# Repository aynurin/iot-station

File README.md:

# Nour Eggboard

This is a main board of a low-power battery powered IoT device controller based on ESP8266 (ESP-WROOM-02) that drives peripheral devices on I2C bus.

Currenly the project is under development and you can help in the following way:

* Suggest new features and report bugs
* Submit pull requests
* Help fund the development by [donating via PayPal](https://www.paypal.com/donate?business=M5DEYMX2BZ4MJ&no_recurring=0&item_name=Help+support+Nour+Eggboard+development&currency_code=USD)

## LICENSE

Currently this project is licensed as  [GNU AGPLv3](./LICENSE). This is intended to be changed to Apache or MIT when I get a better feel of the project and see how it moves forward. I would accept suggestions of a qualified lawyer as I need help figuring out how to move forward.

## How is this helpful

Most prototyping boards are exactly what they say - designed for prototyping and difficult to apply in a production device or if you are a hardcore hobbyist. Unlike those projects, the Eggboard is intended to be a final solution that lets you hook your peripherals to an I2C bus and enjoy a low-power battery operation, wireless charging, and WiFi connectivity out of the box.

Features:

* WiFi capability via ESP8266
* Own I2C port that allows I2C communication, sleep power line, ability to operate when host sleeps, and a host wakeup channel
* Customizable (via resistance change) sleep timer that drives the host and all of the peripherals
* Battery operation
* Wireless and USB-C charging
* USB-C programming via esptool or Arduino IDE (and other compatible IDEs and methods)

## Nour Egg Plant station

The example implementation is a Nour Egg plant ecosystem controller that is under development. This device is going to be commercially available for purchase in 2022 along with free downloadable app and a cloud-based analytics platform.

Key features of the Nour Egg:

* Monitor air quality, soil moisture, and lighting conditions of your home plant
* Low-power operation that runs for months on a single charge, and wireless charging
* WiFi connectivity to report statistics to the cloud and Nour Egg app
* Appealing look and feel in a nice shell and beautiful RGB light indicators

Implemented peripherals:

* Soil moisture sensor based on capacitance sensing using a coplanar capacitor probe
* Air quality sensor
* Light sensor
* LED indicators board driving 18 leds or 6 RGB leds

## Roadmap

The versioning works by bird names, e.g. see [WhatBird.com NA Birds by Size](https://www.whatbird.com/browse/attribute/birds_na_147/51/Size/):

| Milestone | Release Date | Focus |
|---|---|---|
| [Pine Siskin](https://github.com/aynurin/iot-station/milestone/1) | September 2021 | Hardware design |
| [Pygmy Nuthatch](https://github.com/aynurin/iot-station/milestone/2) | December 2021 | PoC Cloud and App |
| [Winter Wren](https://github.com/aynurin/iot-station/milestone/3) | March 2022 | Production feasible enclosure |
| [Hutton's Vireo](https://github.com/aynurin/iot-station/milestone/4) | June 2022 | Production feasible hardware, test board production |
.

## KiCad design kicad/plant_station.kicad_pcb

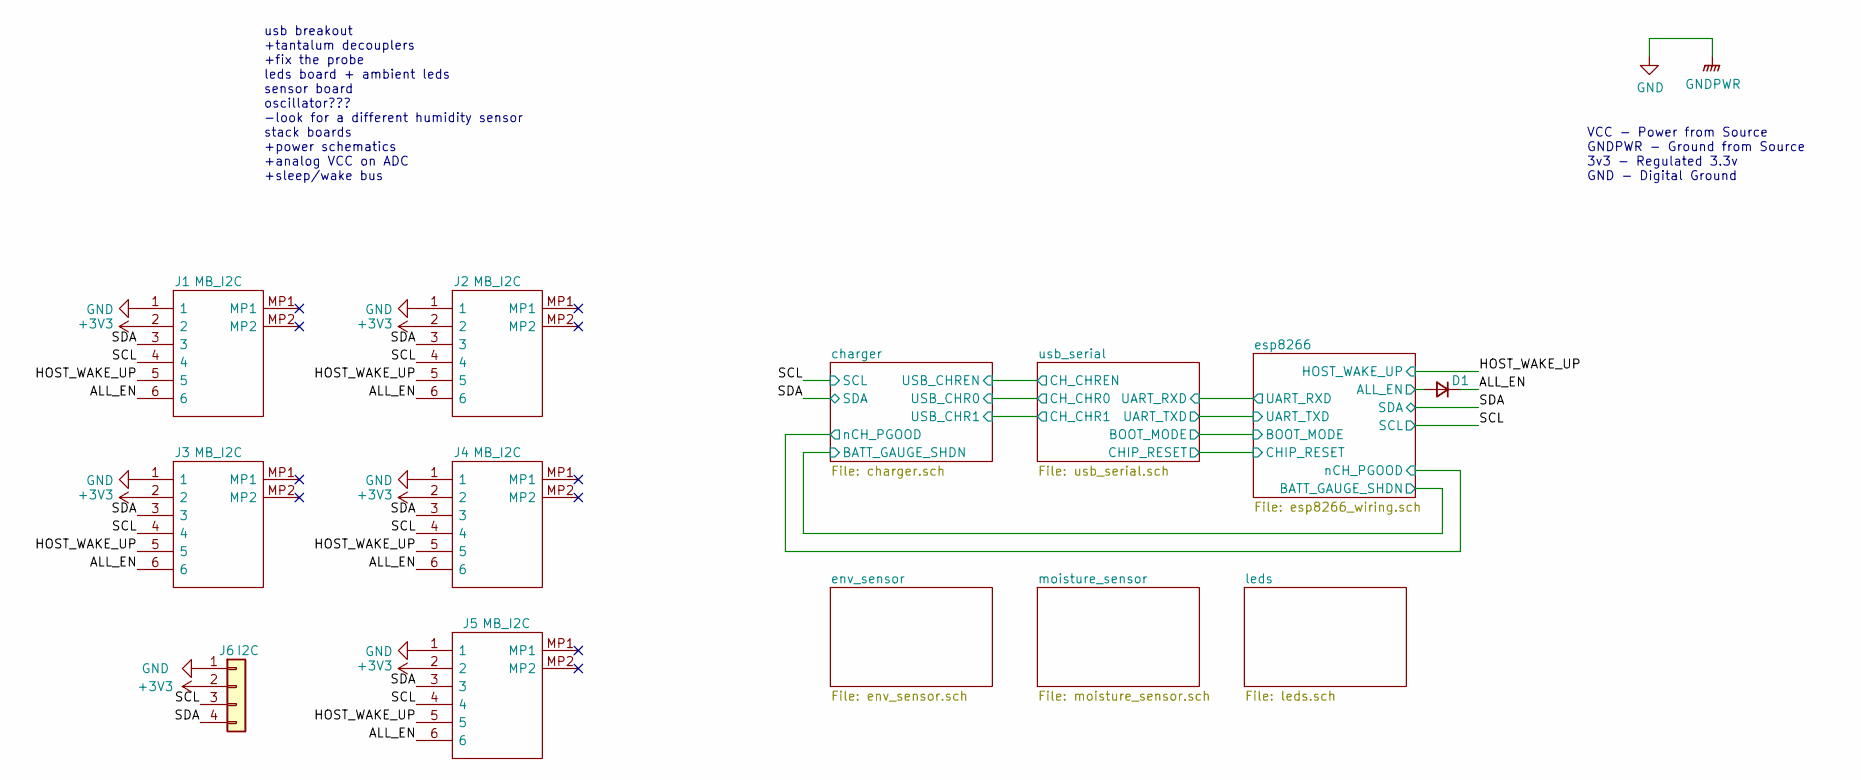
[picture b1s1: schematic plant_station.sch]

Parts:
D1: LS4148; MELF_SOD_80_3_BZT55B13GS08
J1, J2, J3, J4, J5: MB_I2C; Molex_Conn_SMD_01x06_505567_0671; Manufacturer_Part_Number 505567-0671; Mouser Part Number 538-505567-0671
J6: I2C; PinSocket_1x04_P2.54mm_Vertical

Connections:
/ALL_EN: D1.1 (K), J1.6, J2.6, J3.6, J4.6, J5.6
/HOST_WAKE_UP: J1.5, J2.5, J3.5, J4.5, J5.5; also elsewhere on the board
/SCL: J1.4, J2.4, J3.4, J4.4, J5.4, J6.3; also elsewhere on the board
/SDA: J1.3, J2.3, J3.3, J4.3, J5.3, J6.4; also elsewhere on the board
/esp8266/ALL_EN: D1.2 (A); also elsewhere on the board
GND: J1.1, J2.1, J3.1, J4.1, J5.1, J6.1; also elsewhere on the board

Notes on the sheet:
usb breakout +tantalum decouplers +fix the probe leds board + ambient leds sensor board oscillator??? -look for a different humidity sensor stack boards +power schematics +analog VCC on ADC +sleep/wake bus
VCC - Power from Source GNDPWR - Ground from Source 3v3 - Regulated 3.3v GND - Digital Ground

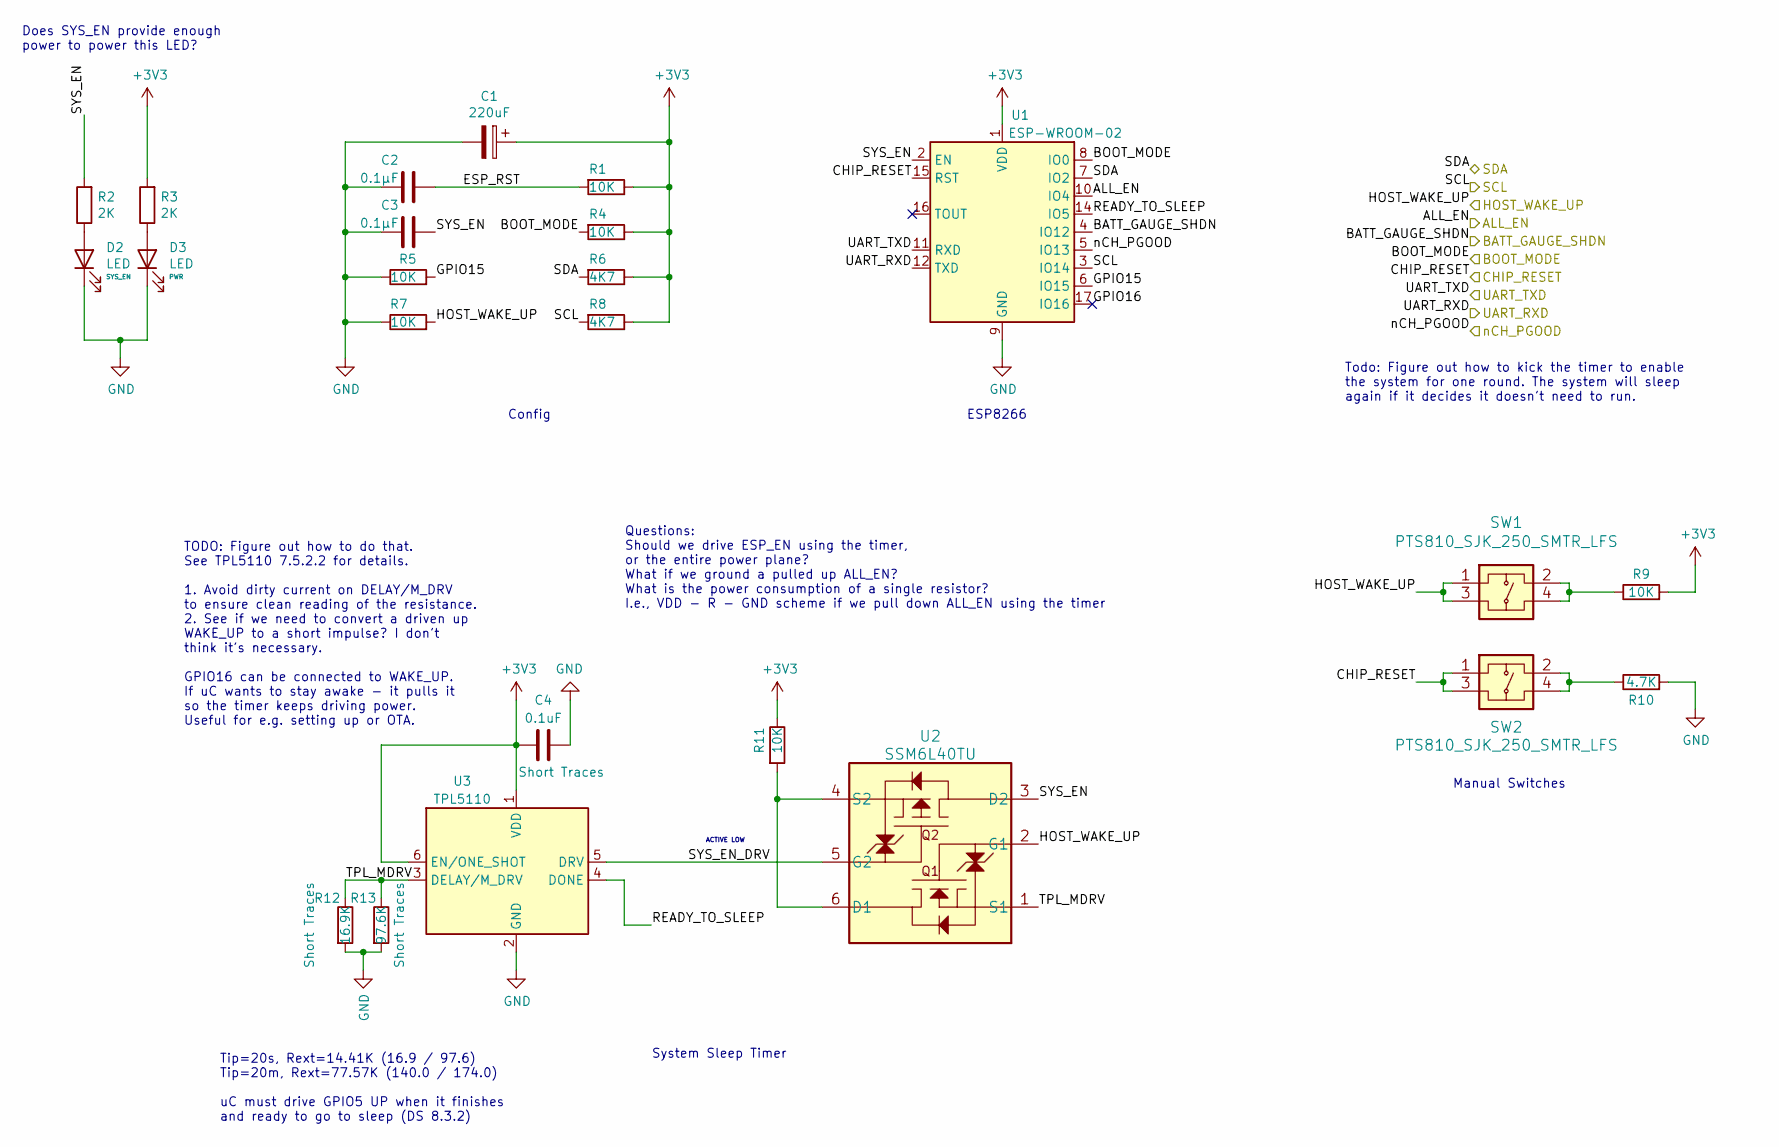
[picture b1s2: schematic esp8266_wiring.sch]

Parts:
C1: 220uF; CP_EIA-3216-18_Kemet-A
C2, C3: 0.1μF; C_1206_3216Metric
C4: 0.1uF; C_1206_3216Metric
D2, D3: LED; LED_0603_1608Metric
R1, R4, R5, R7, R9, R11: 10K; R_0805_2012Metric
R2, R3: 2K; R_0805_2012Metric
R6, R8: 4K7; R_0805_2012Metric
R10: 4.7K; R_0805_2012Metric
R12: 16.9K; R_0805_2012Metric
R13: 97.6K; R_0805_2012Metric
SW1, SW2: PTS810_SJK_250_SMTR_LFS; PTS810SJK250SMTRLFS
U1: ESP-WROOM-02
U2: SSM6L40TU
U3: TPL5110; SOT-23-6

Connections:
/HOST_WAKE_UP: R7.2, SW1.1, SW1.3, U2.2 (G1); also elsewhere on the board
/SCL: R8.2, U1.3 (IO14); also elsewhere on the board
/SDA: R6.2, U1.7 (IO2); also elsewhere on the board
/charger/BATT_GAUGE_SHDN: U1.4 (IO12); also elsewhere on the board
/charger/nCH_PGOOD: U1.5 (IO13); also elsewhere on the board
/esp8266/ALL_EN: U1.10 (IO4); also elsewhere on the board
/esp8266/BOOT_MODE: R4.2, U1.8 (IO0); also elsewhere on the board
/esp8266/CHIP_RESET: SW2.1, SW2.3, U1.15 (RST); also elsewhere on the board
/esp8266/ESP_RST: C2.2, R1.2
/esp8266/GPIO15: R5.2, U1.6 (IO15)
/esp8266/GPIO16: U1.17 (IO16)
/esp8266/READY_TO_SLEEP: U1.14 (IO5), U3.4 (DONE)
/esp8266/SYS_EN: C3.2, R2.2, U1.2 (EN), U2.3 (D2)
/esp8266/SYS_EN_DRV: U2.5 (G2), U3.5 (DRV)
/esp8266/TPL_MDRV: R12.1, R13.1, U2.1 (S1), U3.3 (DELAY/M_DRV)
/esp8266/UART_RXD: U1.12 (TXD); also elsewhere on the board
/esp8266/UART_TXD: U1.11 (RXD); also elsewhere on the board
GND: C1.2, C2.1, C3.1, C4.1, D2.1 (K), D3.1 (K), R5.1, R7.1, R10.2, R12.2, R13.2, U1.9 (GND), U1.13 (GND), U1.18 (GND), U1.19 (GND), U3.2 (GND); also elsewhere on the board
unnamed: D2.2 (A), R2.1
unnamed: D3.2 (A), R3.1
unnamed: R9.1, SW1.2, SW1.4
unnamed: R10.1, SW2.2, SW2.4
unnamed: R11.2, U2.4 (S2), U2.6 (D1)

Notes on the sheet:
Config
System Sleep Timer
Tip=20s, Rext=14.41K (16.9 / 97.6) Tip=20m, Rext=77.57K (140.0 / 174.0) uC must drive GPIO5 UP when it finishes and ready to go to sleep (DS 8.3.2)
TODO: Figure out how to do that. See TPL5110 7.5.2.2 for details. 1. Avoid dirty current on DELAY/M_DRV to ensure clean reading of the resistance. 2. See if we need to convert a driven up WAKE_UP to a short impulse? I don't think it's necessary. GPIO16 can be connected to WAKE_UP. If uC wants to st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
Questions: Should we drive ESP_EN using the timer, or the entire power plane? What if we ground a pulled up ALL_EN? What is the power consumption of a single resistor? I.e., VDD - R - GND scheme if we pull down ALL_EN using the timer
ACTIVE LOW
ESP8266
Does SYS_EN provide enough power to power this LED?
Manual Switches
Todo: Figure out how to kick the timer to enable the system for one round. The system will sleep again if it decides it doesn't need to run.

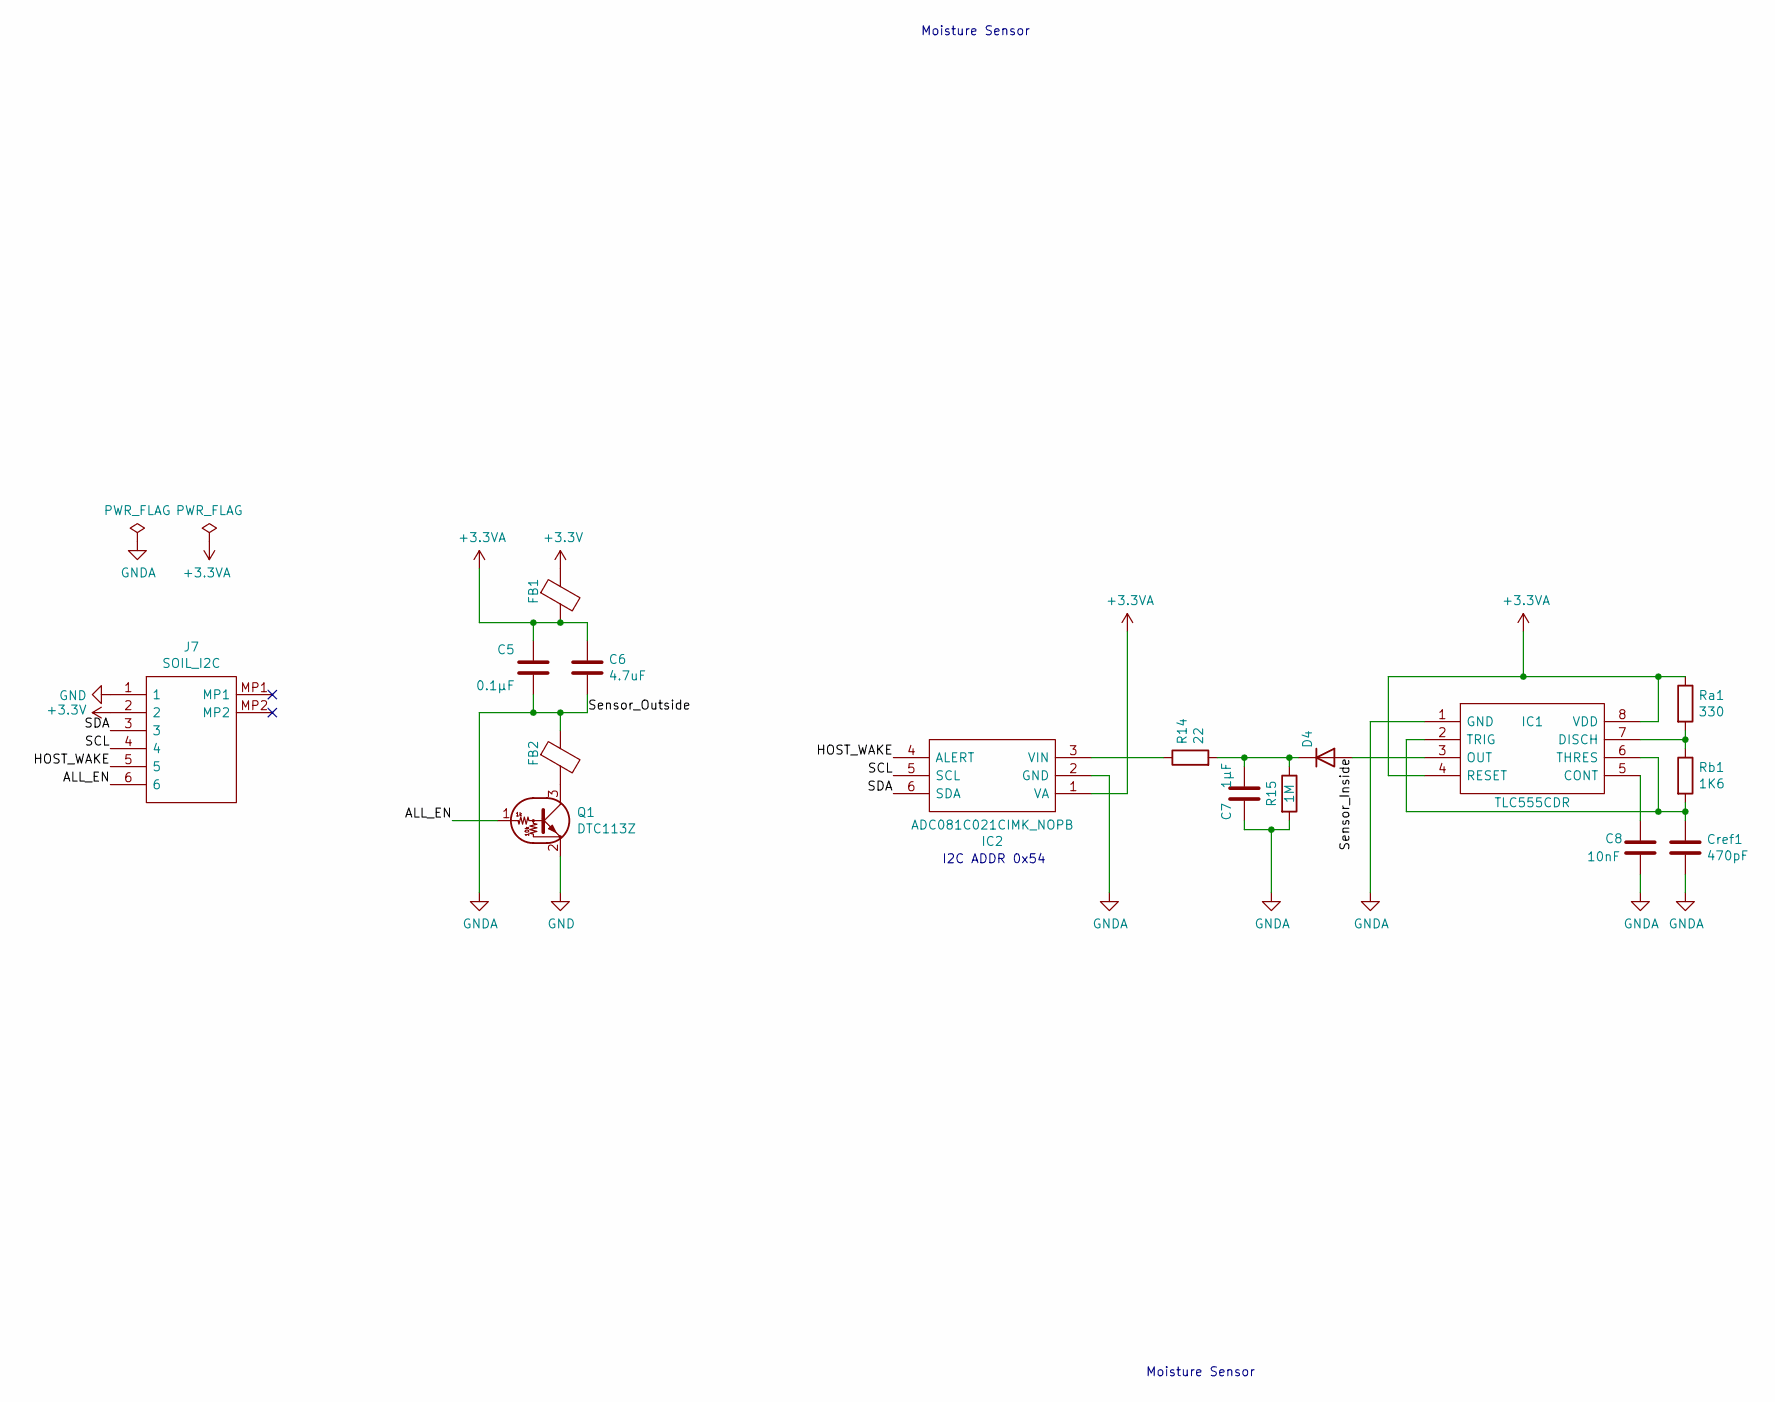
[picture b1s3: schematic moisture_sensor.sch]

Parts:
C5: 0.1μF; C_1206_3216Metric
C6: 4.7uF; C_1206_3216Metric
C7: 1μF; C_1206_3216Metric
C8: 10nF; C_1206_3216Metric
Cref1: 470pF; C_1206_3216Metric
D4: LS4148; MELF_SOD_80_3_BZT55B13GS08
FB1, FB2: BLM21AG601SZ1D; Ferrite_Bead_0805_BLM21
IC1: TLC555CDR; SOIC127P600X175-8N; Mouser Part Number 595-TLC555CDR
IC2: ADC081C021CIMK_NOPB; SOT95P280X110-6N; Mouser Part Number 926-AD081C021CIMKNPB
J7: SOIL_I2C; Molex_Conn_SMD_01x06_505567_0671; Manufacturer_Part_Number 505567-0671; Mouser Part Number 538-505567-0671
Q1: DTC113Z; DTC113ZEBTL
R14: 22; R_0805_2012Metric
R15: 1M; R_1206_3216Metric
Ra1: 330; R_0805_2012Metric
Rb1: 1K6; R_1206_3216Metric

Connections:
+3.3VA: C5.2, C6.1, FB1.2, IC1.4 (RESET), IC1.8 (VDD), IC2.1 (VA), Ra1.1
/moisture_sensor/ALL_EN: J7.6, Q1.1 (B)
/moisture_sensor/HOST_WAKE: IC2.4 (ALERT), J7.5
/moisture_sensor/SCL: IC2.5 (SCL), J7.4
/moisture_sensor/SDA: IC2.6 (SDA), J7.3
/moisture_sensor/Sensor_Inside: D4.2 (A), IC1.3 (OUT)
GND: J7.1, Q1.2 (E); also elsewhere on the board
GNDA: C5.1, C6.2, C7.2, C8.2, Cref1.2, FB2.1, IC1.1 (GND), IC2.2 (GND), R15.2
unnamed: C7.1, D4.1 (K), R14.2, R15.1
unnamed: C8.1, IC1.5 (CONT)
unnamed: Cref1.1, IC1.2 (TRIG), IC1.6 (THRES), Rb1.2
unnamed: FB2.2, Q1.3 (C)
unnamed: IC1.7 (DISCH), Ra1.2, Rb1.1
unnamed: IC2.3 (VIN), R14.1

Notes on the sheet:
Moisture Sensor
I2C ADDR 0x54

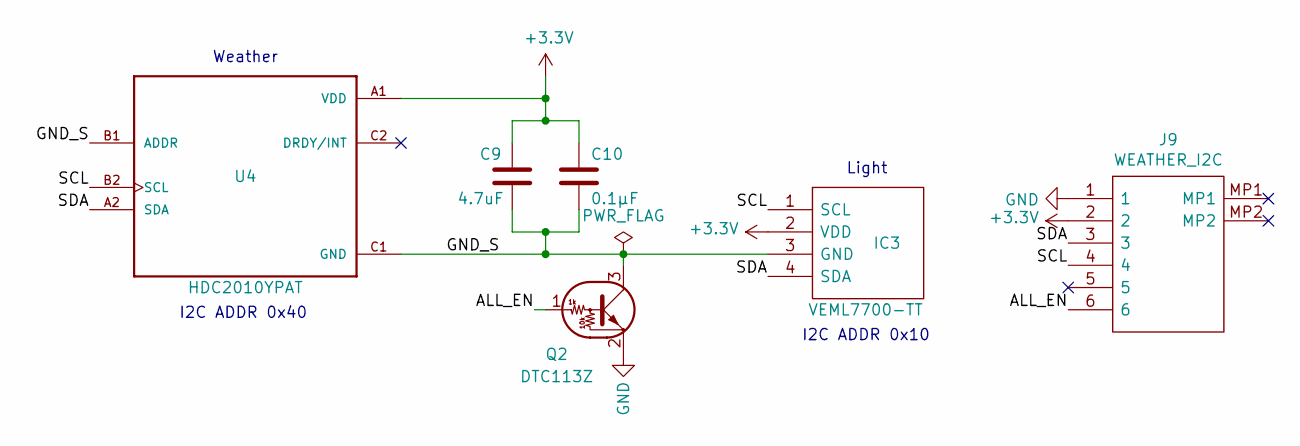
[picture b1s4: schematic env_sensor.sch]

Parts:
C9: 4.7uF; C_1206_3216Metric
C10: 0.1μF; C_1206_3216Metric
IC3: VEML7700-TT; VEML7700; Mouser Part Number 78-VEML7700-TT
J9: WEATHER_I2C; Molex_Conn_SMD_01x06_505567_0671; Manufacturer_Part_Number 505567-0671; Mouser Part Number 538-505567-0671
Q2: DTC113Z; DTC113ZEBTL
U4: HDC2010YPAT; BGA6C100X50P2X3_146X146X67

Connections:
/env_sensor/ALL_EN: J9.6, Q2.1 (B)
/env_sensor/GND_S: C9.2, C10.2, IC3.3 (GND), Q2.3 (C), U4.B1 (ADDR), U4.C1 (GND)
/env_sensor/SCL: IC3.1 (SCL), J9.4, U4.B2 (SCL)
/env_sensor/SDA: IC3.4 (SDA), J9.3, U4.A2 (SDA)
GND: J9.1, Q2.2 (E); also elsewhere on the board

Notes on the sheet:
Light
I2C ADDR 0x10
Weather
I2C ADDR 0x40

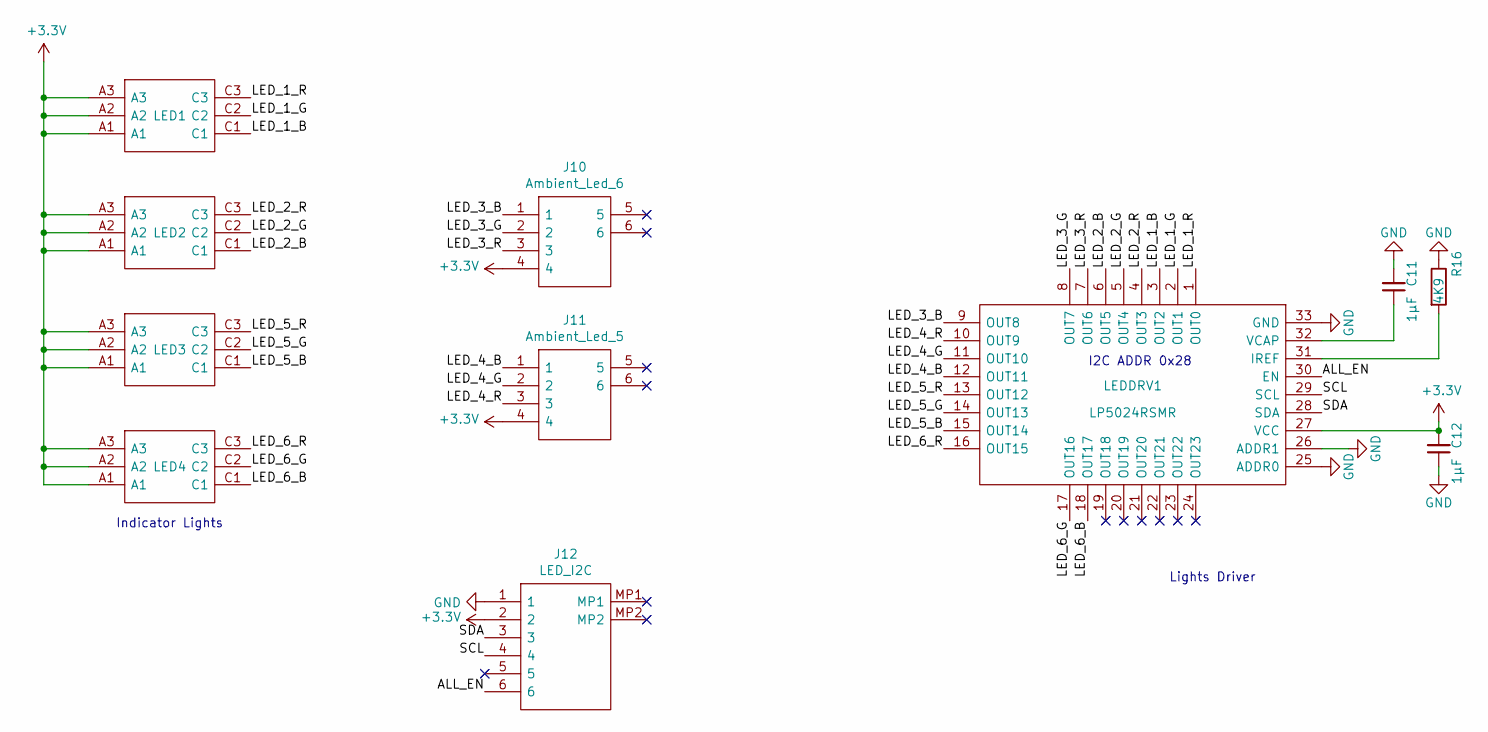
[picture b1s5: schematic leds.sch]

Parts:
C11, C12: 1μF; C_1206_3216Metric
J10: Ambient_Led_6; Molex_Conn_SMD_01x04_505567_0471; Manufacturer_Part_Number 505567-0471; Mouser Part Number 538-505567-0471
J11: Ambient_Led_5; Molex_Conn_SMD_01x04_505567_0471; Manufacturer_Part_Number 505567-0471; Mouser Part Number 538-505567-0471
J12: LED_I2C; Molex_Conn_SMD_01x06_505567_0671; Manufacturer_Part_Number 505567-0671; Mouser Part Number 538-505567-0671
LED1, LED2, LED3, LED4: KRTBLSLPS1.32-VUVX-EQ+BTBV-D8+TWTZ-L1-B; KRTBLSLPS132VUVXEQBTBVD8TWTZL1B; Mouser Part Number 720-KRTBLSLPS13A0062
LEDDRV1: LP5024RSMR; QFN40P400X400X100-33N-D; Mouser Part Number 595-LP5024RSMR
R16: 4K9; R_0805_2012Metric

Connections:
/leds/ALL_EN: J12.6, LEDDRV1.30 (EN)
/leds/LED_1_B: LED1.C1, LEDDRV1.3 (OUT2)
/leds/LED_1_G: LED1.C2, LEDDRV1.2 (OUT1)
/leds/LED_1_R: LED1.C3, LEDDRV1.1 (OUT0)
/leds/LED_2_B: LED2.C1, LEDDRV1.6 (OUT5)
/leds/LED_2_G: LED2.C2, LEDDRV1.5 (OUT4)
/leds/LED_2_R: LED2.C3, LEDDRV1.4 (OUT3)
/leds/LED_3_B: J10.1, LEDDRV1.9 (OUT8)
/leds/LED_3_G: J10.2, LEDDRV1.8 (OUT7)
/leds/LED_3_R: J10.3, LEDDRV1.7 (OUT6)
/leds/LED_4_B: J11.1, LEDDRV1.12 (OUT11)
/leds/LED_4_G: J11.2, LEDDRV1.11 (OUT10)
/leds/LED_4_R: J11.3, LEDDRV1.10 (OUT9)
/leds/LED_5_B: LED3.C1, LEDDRV1.15 (OUT14)
/leds/LED_5_G: LED3.C2, LEDDRV1.14 (OUT13)
/leds/LED_5_R: LED3.C3, LEDDRV1.13 (OUT12)
/leds/LED_6_B: LED4.C1, LEDDRV1.18 (OUT17)
/leds/LED_6_G: LED4.C2, LEDDRV1.17 (OUT16)
/leds/LED_6_R: LED4.C3, LEDDRV1.16 (OUT15)
/leds/SCL: J12.4, LEDDRV1.29 (SCL)
/leds/SDA: J12.3, LEDDRV1.28 (SDA)
GND: C11.2, C12.1, J12.1, LEDDRV1.25 (ADDR0), LEDDRV1.26 (ADDR1), LEDDRV1.33 (GND), R16.1; also elsewhere on the board
unnamed: C11.1, LEDDRV1.32 (VCAP)
unnamed: LEDDRV1.31 (IREF), R16.2

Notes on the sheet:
Indicator Lights
I2C ADDR 0x28
Lights Driver

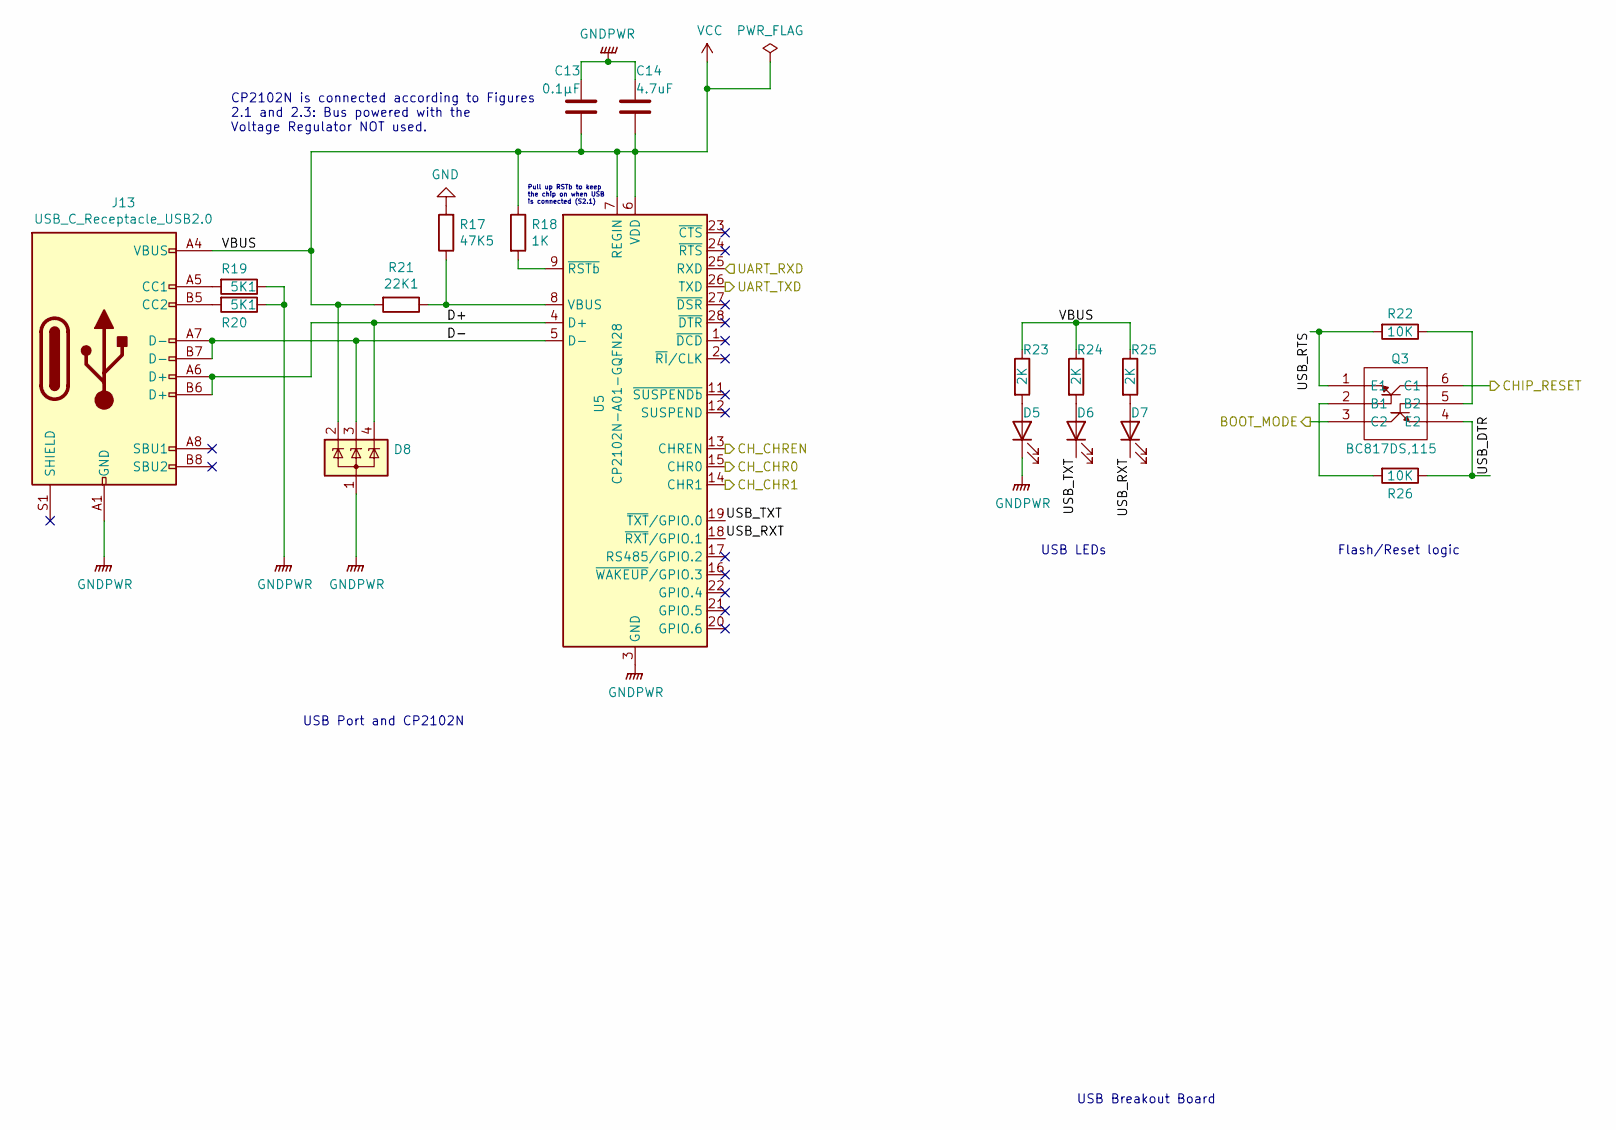
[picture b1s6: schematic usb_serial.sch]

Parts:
C13: 0.1μF; C_1206_3216Metric
C14: 4.7uF; C_1206_3216Metric
D5: 150060AS75000; LED_0603_1608Metric
D6: 150060BS75020; LED_0603_1608Metric
D7: 150060VS75000; LED_0603_1608Metric
D8: SP0503BAHT; SOT-143
J13: USB_C_Receptacle_USB2.0; CUI_UJ31-CH-3-SMT-TR
Q3: BC817DS,115; SOT95P275X110-6N; Manufacturer_Part_Number BC817DS,115; Mouser Part Number 771-BC817DS115
R17: 47K5; R_0805_2012Metric
R18: 1K; R_0805_2012Metric
R19, R20: 5K1; R_0805_2012Metric
R21: 22K1; R_0805_2012Metric
R22, R26: 10K; R_0805_2012Metric
R23, R24, R25: 2K; R_0805_2012Metric
U5: CP2102N-A01-GQFN28; QFN-28-1EP_5x5mm_P0.5mm_EP3.35x3.35mm

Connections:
/esp8266/BOOT_MODE: Q3.3 (C2); also elsewhere on the board
/esp8266/CHIP_RESET: Q3.6 (C1); also elsewhere on the board
/esp8266/UART_RXD: U5.25 (RXD); also elsewhere on the board
/esp8266/UART_TXD: U5.26 (TXD); also elsewhere on the board
/usb_serial/CH_CHR0: U5.15 (CHR0); also elsewhere on the board
/usb_serial/CH_CHR1: U5.14 (CHR1); also elsewhere on the board
/usb_serial/CH_CHREN: U5.13 (CHREN); also elsewhere on the board
/usb_serial/D+: D8.4 (K), J13.A6 (D+), J13.B6 (D+), U5.4 (D+)
/usb_serial/D-: D8.3 (K), J13.A7 (D-), J13.B7 (D-), U5.5 (D-)
/usb_serial/USB_DTR: Q3.4 (E2), R26.1
/usb_serial/USB_RTS: Q3.1 (E1), R22.2
/usb_serial/USB_RXT: D7.1 (K), U5.18 (~RXT~/GPIO.1)
/usb_serial/USB_TXT: D6.1 (K), U5.19 (~TXT~/GPIO.0)
GND: C13.2, C14.1, D5.1 (K), D8.1 (A), J13.A1 (GND), J13.A12 (GND), J13.B1 (GND), J13.B12 (GND), R17.2, R19.1, R20.1, U5.3 (GND), U5.29 (GND); also elsewhere on the board
unnamed: D5.2 (A), R23.2
unnamed: D6.2 (A), R24.2
unnamed: D7.2 (A), R25.2
unnamed: J13.A5 (CC1), R19.2
unnamed: J13.B5 (CC2), R20.2
unnamed: Q3.2 (B1), R26.2
unnamed: Q3.5 (B2), R22.1
unnamed: R17.1, R21.1, U5.8 (VBUS)
unnamed: R18.2, U5.9 (~RSTb)
VCC: C13.1, C14.2, D8.2 (K), J13.A4 (VBUS), J13.A9 (VBUS), J13.B4 (VBUS), J13.B9 (VBUS), R18.1, R21.2, R23.1, R24.1, R25.1, U5.6 (VDD), U5.7 (REGIN); also elsewhere on the board

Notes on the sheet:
USB Breakout Board
USB LEDs
Pull up RSTb to keep the chip on when USB is connected (S2.1)
CP2102N is connected according to Figures 2.1 and 2.3: Bus powered with the Voltage Regulator NOT used.
Flash/Reset logic
USB Port and CP2102N

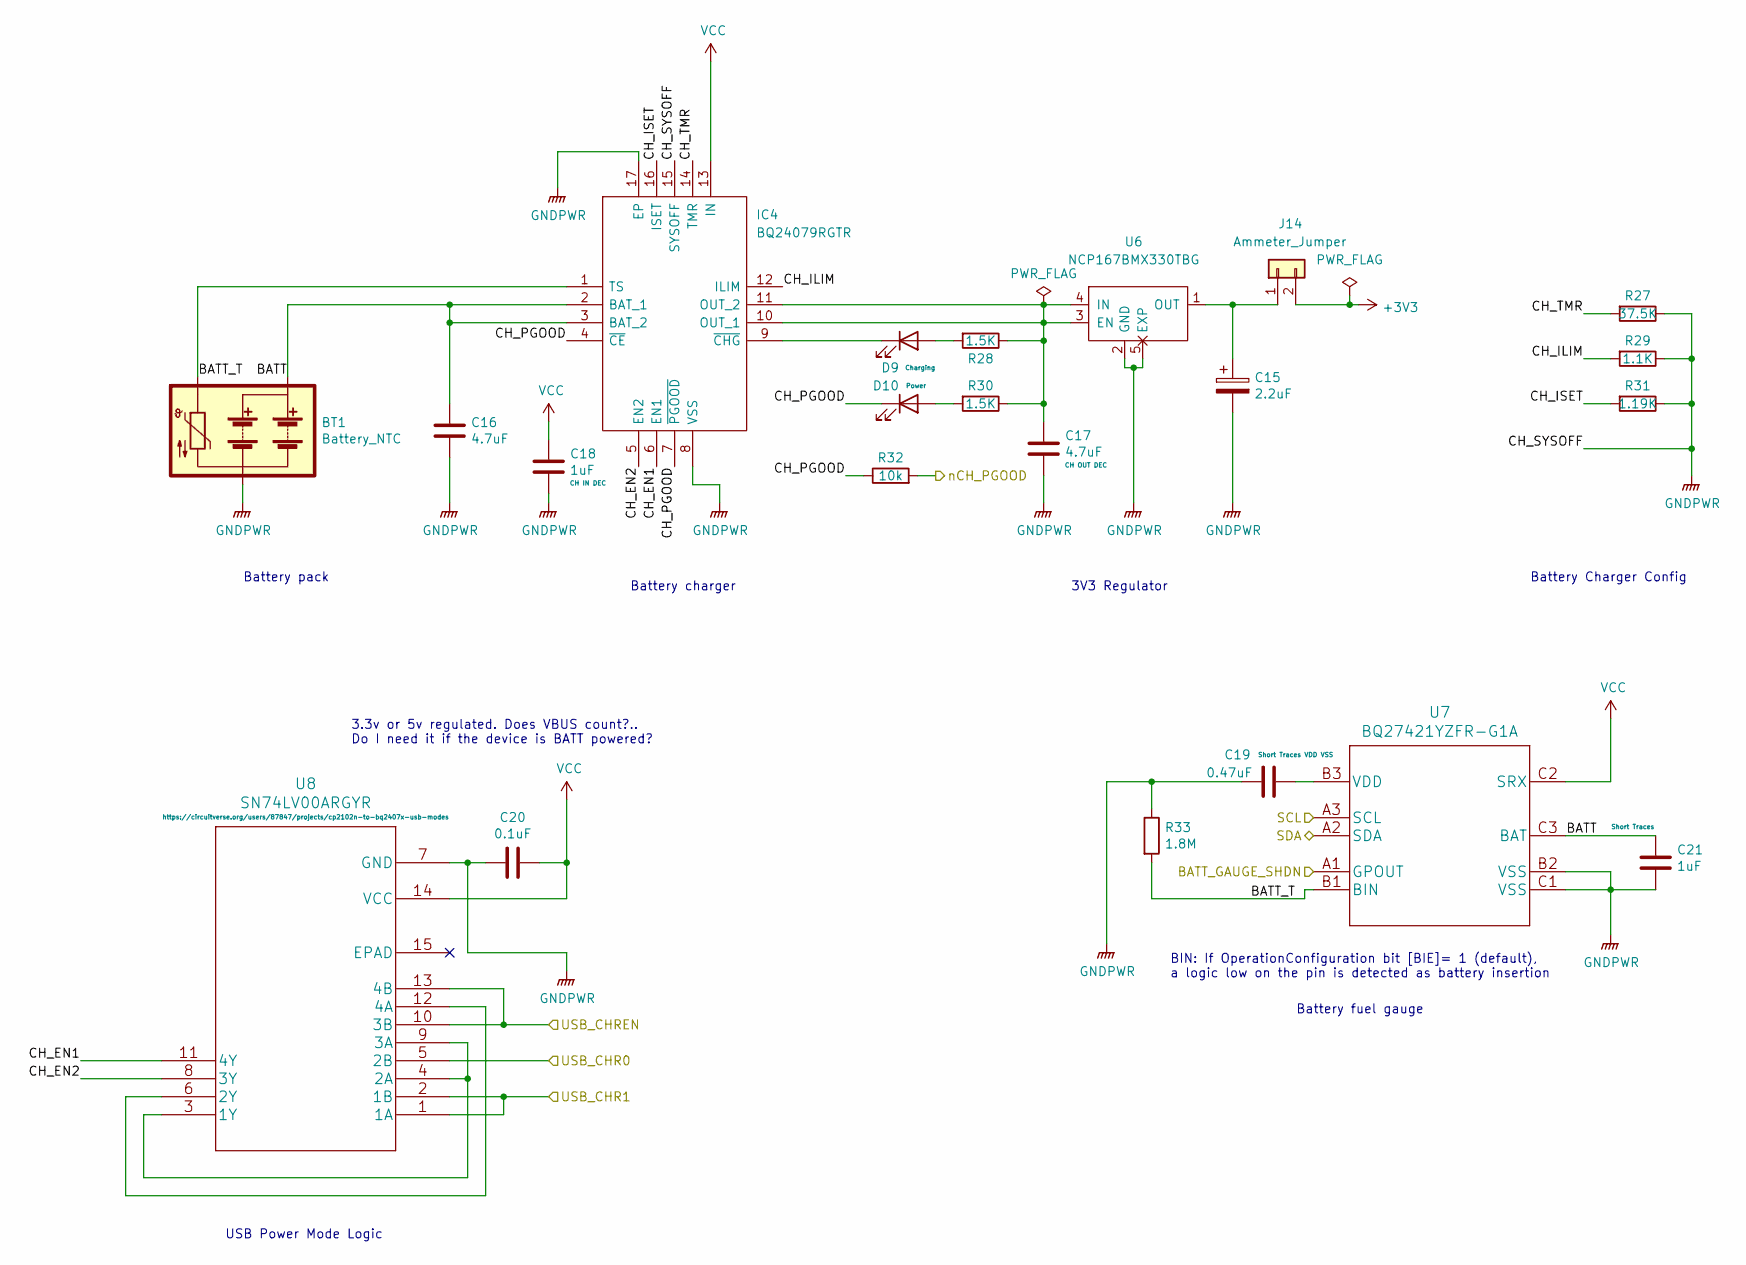
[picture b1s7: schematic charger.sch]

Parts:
BT1: Battery_NTC; JST_EH_B3B-EH-A_1x03_P2.50mm_Vertical
C15: 2.2uF; C_1206_3216Metric
C16, C17: 4.7uF; C_1206_3216Metric
C18, C21: 1uF; C_1206_3216Metric
C19: 0.47uF; C_1206_3216Metric
C20: 0.1uF; C_1206_3216Metric
D9, D10: LED; LED_0603_1608Metric
IC4: BQ24079RGTR; QFN50P300X300X100-17N-D; Manufacturer_Part_Number BQ24079RGTR; Mouser Part Number 595-BQ24079RGTR
J14: Ammeter_Jumper; PinHeader_1x02_P2.54mm_Vertical
R27: 37.5K; R_0805_2012Metric
R28, R30: 1.5K; R_0805_2012Metric
R29: 1.1K; R_0805_2012Metric
R31: 1.19K; R_0805_2012Metric
R32: 10k; R_0805_2012Metric
R33: 1.8M; R_0805_2012Metric
U6: NCP167BMX330TBG; REG_NCP167BMX330TBG
U7: BQ27421YZFR-G1A
U8: SN74LV00ARGYR

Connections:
/SCL: U7.A3 (SCL); also elsewhere on the board
/SDA: U7.A2 (SDA); also elsewhere on the board
/charger/BATT: BT1.3 (+), C16.1, C21.1, IC4.2 (BAT_1), IC4.3 (BAT_2), U7.C3 (BAT)
/charger/BATT_GAUGE_SHDN: U7.A1 (GPOUT); also elsewhere on the board
/charger/BATT_T: BT1.2 (TH_NTC), IC4.1 (TS), R33.2, U7.B1 (BIN)
/charger/CH_EN1: IC4.6 (EN1), U8.11 (4Y)
/charger/CH_EN2: IC4.5 (EN2), U8.8 (3Y)
/charger/CH_ILIM: IC4.12 (ILIM), R29.2
/charger/CH_ISET: IC4.16 (ISET), R31.2
/charger/CH_PGOOD: D10.1 (K), IC4.4 (~CE), IC4.7 (~PGOOD), R32.1
/charger/CH_TMR: IC4.14 (TMR), R27.2
/charger/nCH_PGOOD: R32.2; also elsewhere on the board
/usb_serial/CH_CHR0: U8.5 (2B); also elsewhere on the board
/usb_serial/CH_CHR1: U8.1 (1A), U8.2 (1B); also elsewhere on the board
/usb_serial/CH_CHREN: U8.10 (3B), U8.13 (4B); also elsewhere on the board
GND: BT1.1 (-), C15.2, C16.2, C17.2, C18.1, C19.2, C20.2, C21.2, IC4.8 (VSS), IC4.15 (SYSOFF), IC4.17 (EP), R27.1, R29.1, R31.1, R33.1, U6.2 (GND), U6.5 (EXP), U7.B2 (VSS), U7.C1 (VSS), U8.7 (GND); also elsewhere on the board
unnamed: C15.1, J14.1, U6.1 (OUT)
unnamed: C17.1, IC4.10 (OUT_1), IC4.11 (OUT_2), R28.1, R30.1, U6.3 (EN), U6.4 (IN)
unnamed: C19.1, U7.B3 (VDD)
unnamed: D9.1 (K), IC4.9 (~CHG)
unnamed: D9.2 (A), R28.2
unnamed: D10.2 (A), R30.2
unnamed: U8.3 (1Y), U8.4 (2A), U8.9 (3A)
unnamed: U8.6 (2Y), U8.12 (4A)
VCC: C18.2, C20.1, IC4.13 (IN), U7.C2 (SRX), U8.14 (VCC); also elsewhere on the board

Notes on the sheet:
Battery fuel gauge
Battery pack
3.3v or 5v regulated. Does VBUS count?.. Do I need it if the device is BATT powered?
3V3 Regulator
BIN: If OperationConfiguration bit [BIE]= 1 (default), a logic low on the pin is detected as battery insertion
Battery charger
USB Power Mode Logic
Battery Charger Config

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
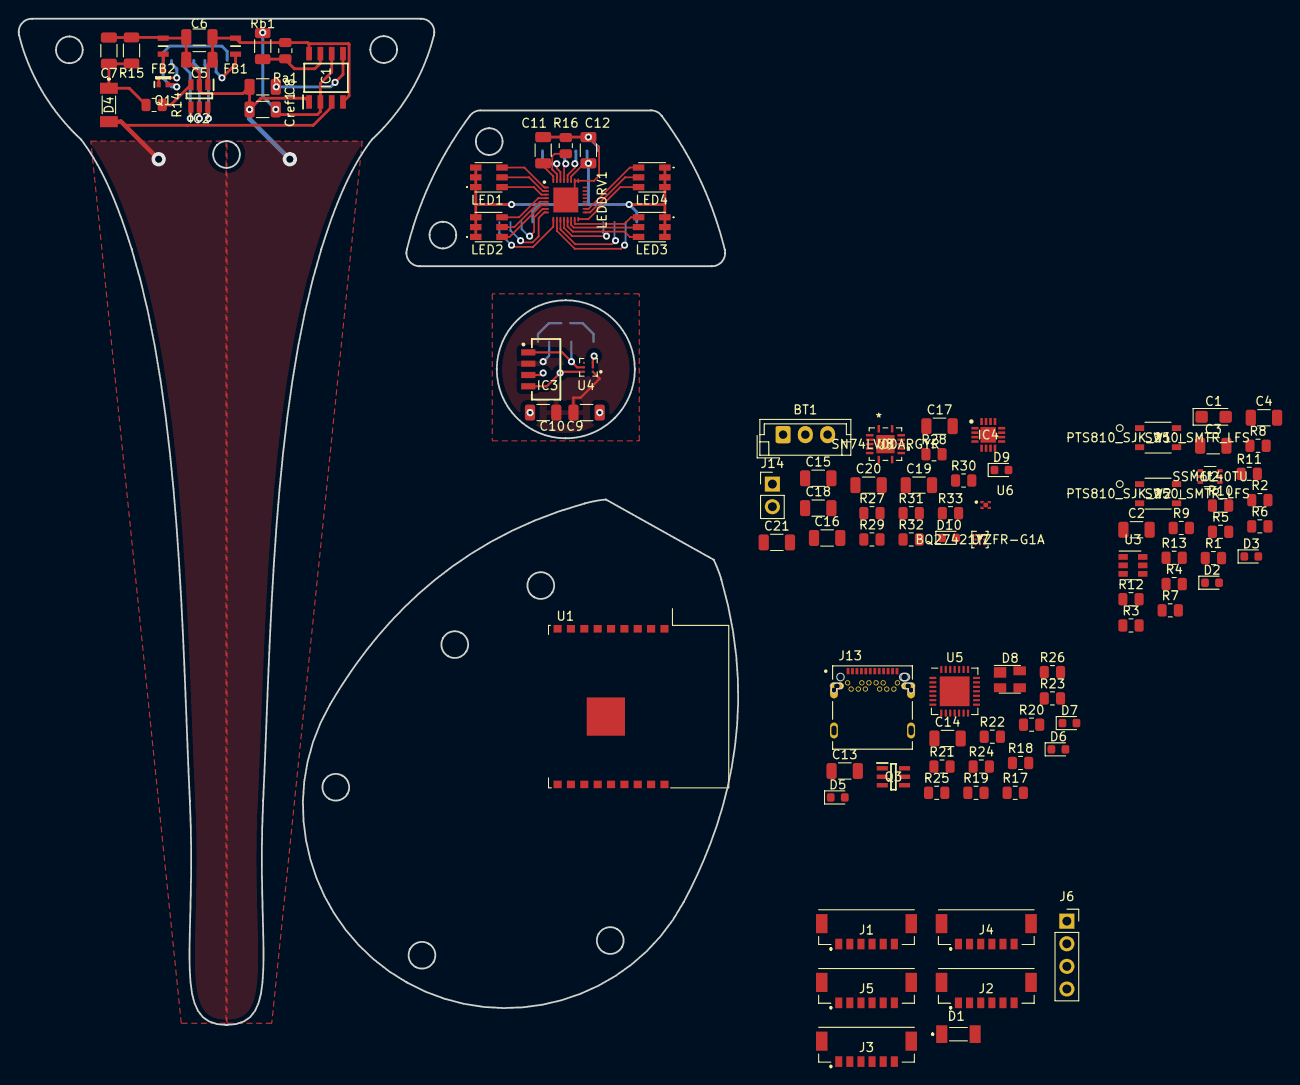
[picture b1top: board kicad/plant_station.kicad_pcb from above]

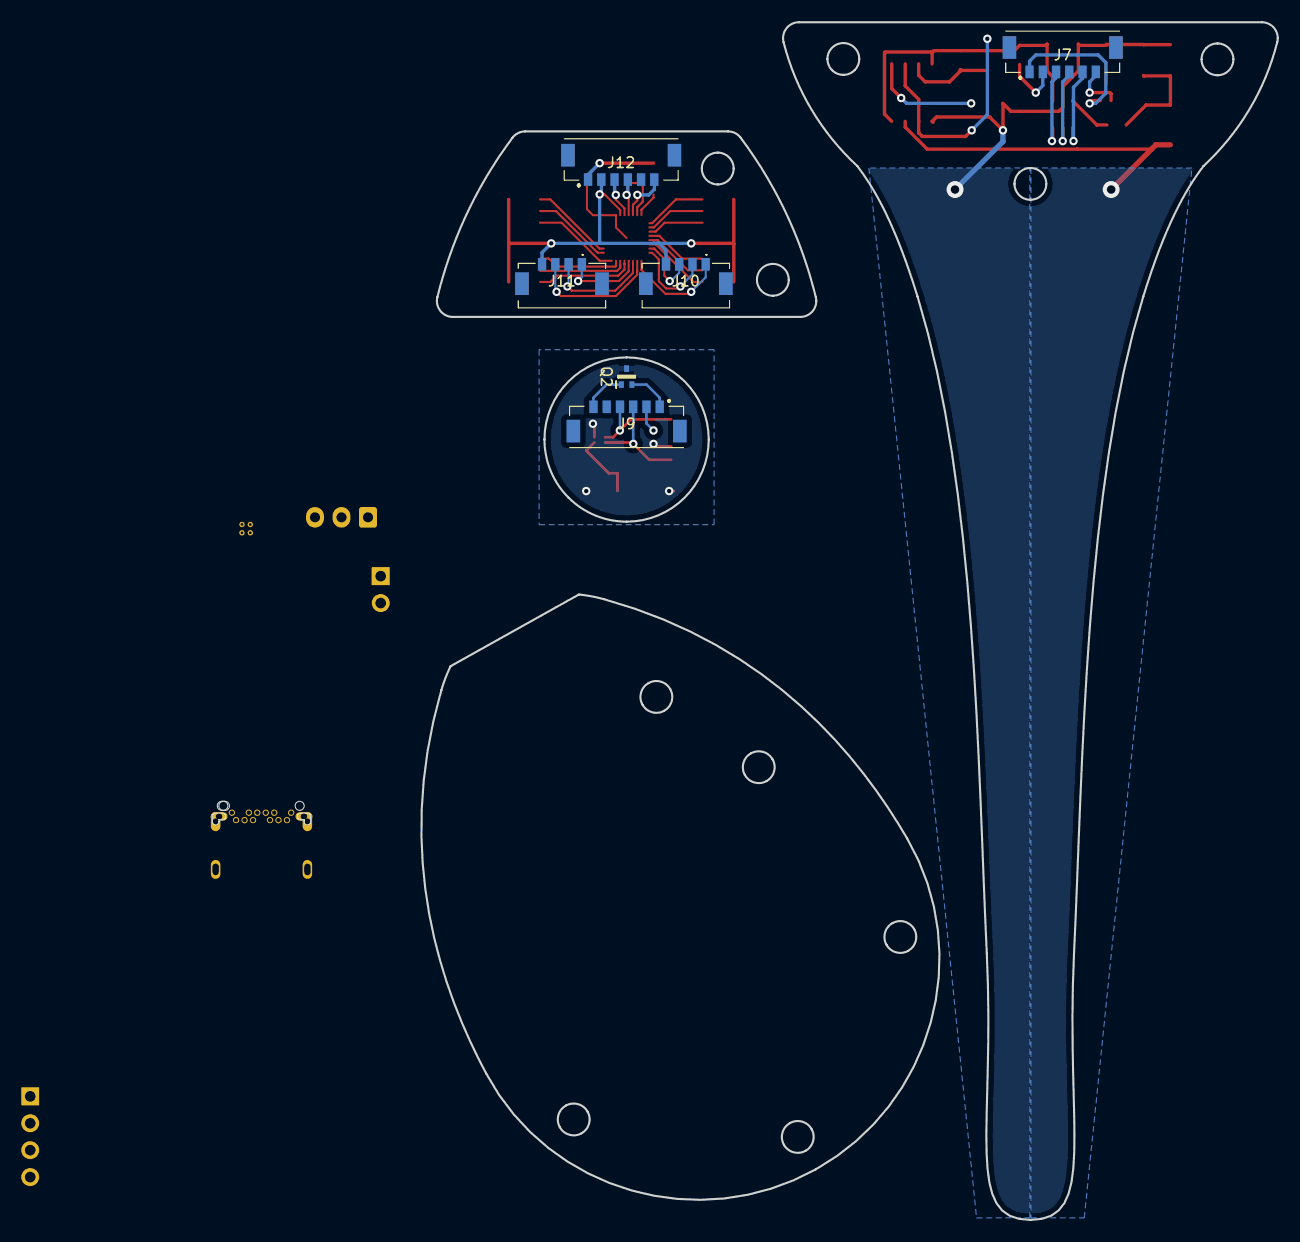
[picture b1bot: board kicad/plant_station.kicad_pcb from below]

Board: 2 copper layers, 100.5 x 113.0 mm, 105 parts (6 on the bottom side), 99 nets.

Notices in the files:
parts and their libraries:
Copyright 2021 Accelerated Designs. All rights reserved.
